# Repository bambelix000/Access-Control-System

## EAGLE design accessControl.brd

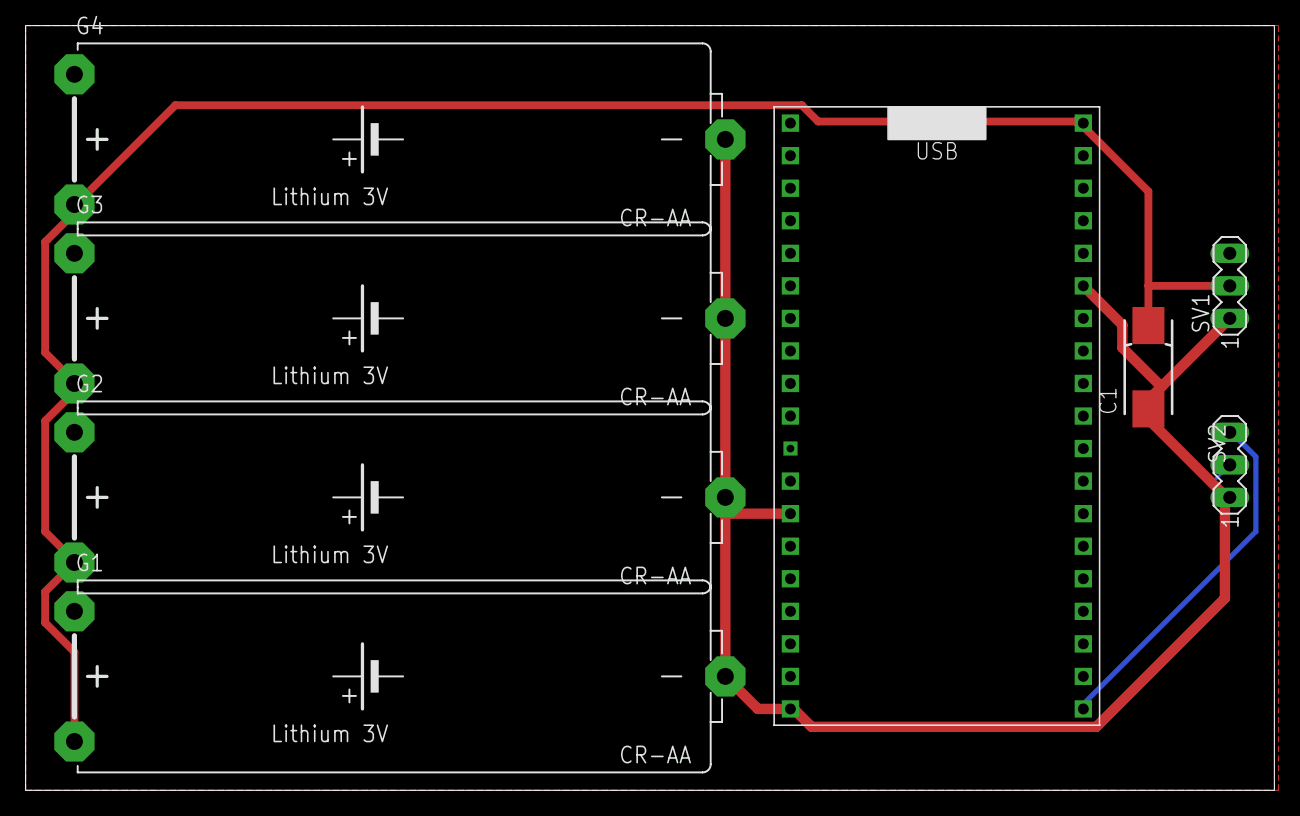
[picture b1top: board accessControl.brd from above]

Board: 2 copper layers, 97.5 x 59.7 mm, 8 parts (0 on the bottom side), 4 nets.

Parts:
C1: 470uF; 085CS_1AR
G1, G2, G3, G4: CR-AA; CRAA
SV1, SV2: MA03-1
U$1: ESP32

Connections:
+3V3: SV2.3, U$1.3.3V
+5V: C1.+, G1.+, G2.+, G3.+, G4.+, SV1.2, U$1.5V
GND: C1.-, G1.-, G2.-, G3.-, G4.-, SV1.1, SV2.1, U$1.GND1, U$1.GND2, U$1.GND3
unnamed: SV2.2, U$1.GPIO32

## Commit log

2026-04-09 init
2026-04-09 Entities and createUser
2026-04-09 works
2026-04-14 server done and app
2026-05-06 esp32 code
